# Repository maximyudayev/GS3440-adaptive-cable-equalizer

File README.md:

# SDI Adaptive Cable Equalizer - Semtech GS3440
This equalizer board was built as part of my Hardware Design course at KU Leuven - Campus GroupT in academic year 2020-2021, taught by the awesome Gorik :wink:

PCB front side:

PCB back side:

Mechanical layer details:

50 Ohm trace width:

75 Ohm trace width:

All the design files are under GPL3 and can be freely used for personal projects where this device can be of use.

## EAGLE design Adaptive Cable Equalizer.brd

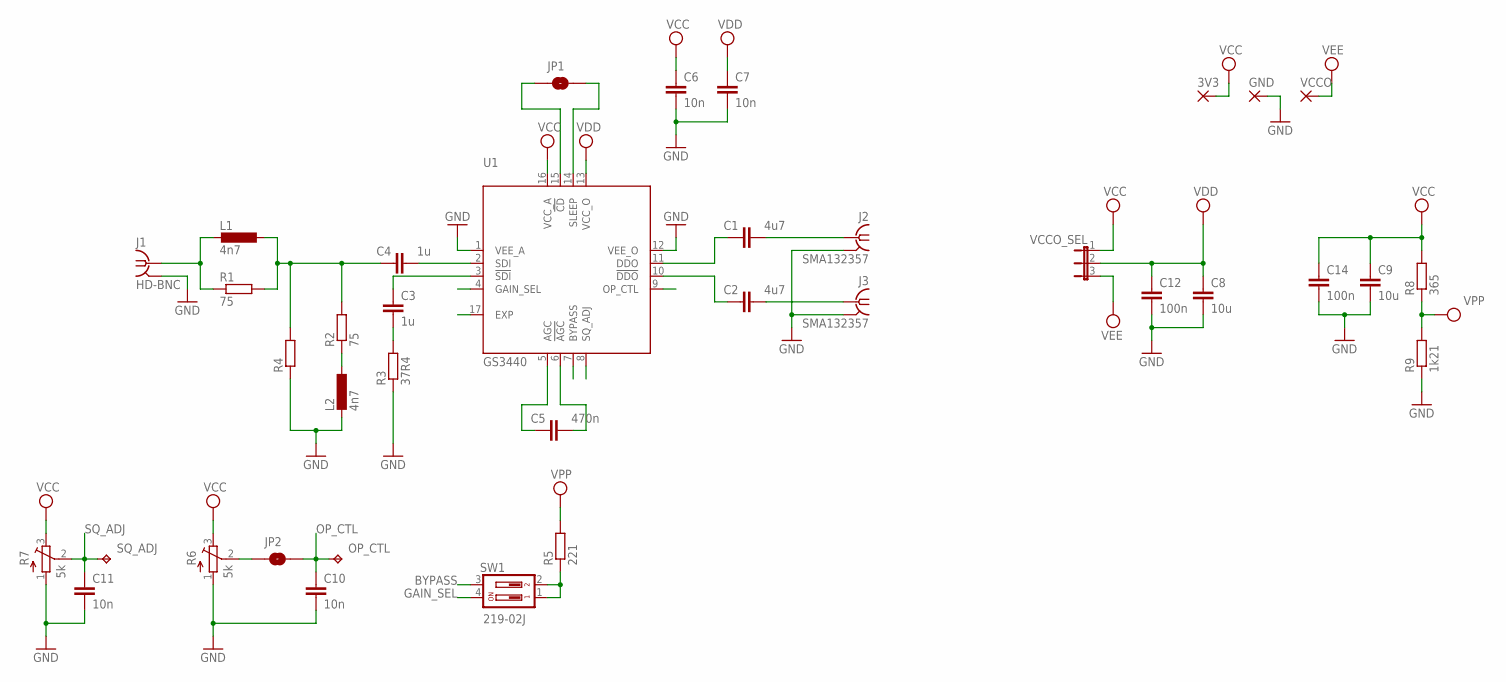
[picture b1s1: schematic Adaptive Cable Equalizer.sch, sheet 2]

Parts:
3V3: TAB_37800568(MSTIN); HOLE_1-3
C1, C2: 4u7; 0402
C3, C4: 1u; 0402
C5: 470n; 0402
C6, C7, C10, C11: 10n; 0402
C8, C9: 10u; C0805K
C12, C14: 100n; 0402
GND: TAB_37800568(MSTIN); HOLE_1-3
J1: HD-BNC; 034_1018_12G
J2, J3: SMA132357; SMA
JP1, JP2: SMD-JUMPER
L1, L2: 4n7; 0402
OP_CTL: TPTP06R; TP06R
R1, R2: 75; 0402
R3: 37R4; 0402
R4: R0402; 0402
R5: 221; 0402
R6, R7: 5k; 3223W
R8: 365; 0402
R9: 1k21; 0402
SQ_ADJ: TPTP06R; TP06R
SW1: 219-02J; CTS-219-02J
U1: GS3440; QFN65P400X400X90-17T260N
VCCO: TAB_37800568(MSTIN); HOLE_1-3
VCCO_SEL: JP2E; JP2

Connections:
!CD: JP1.P$1 (1), U1.15 (!CD)
BYPASS: SW1.3, U1.7 (BYPASS)
GAIN_SEL: SW1.4, U1.4 (GAIN_SEL)
GND: C6.2, C7.2, C8.2, C9.2, C10.2, C11.2, C12.2, C14.2, GND.P$1, J1.G@1 (2), J1.G@2 (2), J1.G@3 (2), J1.G@4 (2), J2.G@1 (2), J2.G@2 (2), J2.G@3 (2), J2.G@4 (2), J3.G@1 (2), J3.G@2 (2), J3.G@3 (2), J3.G@4 (2), L2.2, R3.1, R4.1, R6.1 (A), R7.1 (A), R9.1, U1.1 (VEE_A), U1.12 (VEE_O), U1.17 (EXP)
unnamed: C2.2, J3.1
unnamed: C1.2, J2.1
unnamed: C2.1, U1.10 (!DDO)
unnamed: C1.1, U1.11 (DDO)
unnamed: J1.P$1 (1), L1.2, R1.1
unnamed: C4.1, L1.1, R1.2, R2.2, R4.2
unnamed: C3.1, U1.3 (!SDI)
unnamed: C4.2, U1.2 (SDI)
unnamed: L2.1, R2.1
unnamed: C5.1, U1.5 (AGC)
unnamed: C3.2, R3.2
unnamed: C5.2, U1.6 (!AGC)
unnamed: JP2.P$1 (1), R6.2 (S)
unnamed: JP1.P$2 (2), U1.14 (SLEEP)
unnamed: R5.1, SW1.1, SW1.2
OP_CTL: C10.1, JP2.P$2 (2), OP_CTL.TP, U1.9 (OP_CTL)
SQ_ADJ: C11.1, R7.2 (S), SQ_ADJ.TP, U1.8 (SQ_ADJ)
VCC: 3V3.P$1, C6.1, C9.1, C14.1, R6.3 (E), R7.3 (E), R8.2, U1.16 (VCC_A), VCCO_SEL.1
VDD: C7.1, C8.1, C12.1, U1.13 (VCC_O), VCCO_SEL.2
VEE: VCCO.P$1, VCCO_SEL.3
VPP: R5.2, R8.1, R9.2

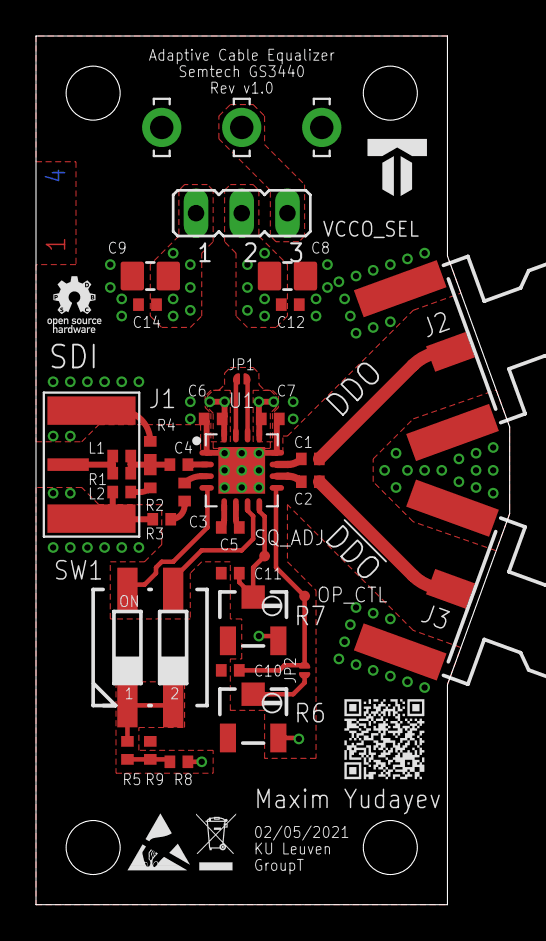
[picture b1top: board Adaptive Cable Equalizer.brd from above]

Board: 4 copper layers, 26.3 x 48.3 mm, 37 parts (0 on the bottom side), 25 nets.

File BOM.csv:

"Qty";"Value";"Device";"Package";"Parts";"Description";"";
"1";"";"JP2E";"JP2";"VCCO_SEL";"JUMPER";"";
"1";"";"R0402";"0402";"R4";"";"";
"2";"100n";"C0402";"0402";"C12, C14";"";"";
"4";"10n";"C0402";"0402";"C6, C7, C10, C11";"";"";
"2";"10u";"C-EUC0805K";"C0805K";"C8, C9";"CAPACITOR, European symbol";"";
"1";"1k21";"R0402";"0402";"R9";"";"";
"2";"1u";"C0402";"0402";"C3, C4";"";"";
"1";"219-02J";"219-02J";"CTS-219-02J";"SW1";"Surface Mount DIP Switch Series 219 SMT";"";
"1";"221";"R0402";"0402";"R5";"";"";
"1";"365";"R0402";"0402";"R8";"";"";
"1";"37R4";"R0402";"0402";"R3";"";"";
"1";"470n";"C0402";"0402";"C5";"";"";
"2";"4n7";"L0402";"0402";"L1, L2";"";"";
"2";"4u7";"C0402";"0402";"C1, C2";"";"";
"2";"5k";"TRIM_EU-3223W";"3223W";"R6, R7";"POTENTIOMETER";"";
"2";"75";"R0402";"0402";"R1, R2";"";"";
"1";"GS3440";"GS3440";"QFN65P400X400X90-17T260N";"U1";"Adaptive Cable Equalizer";"";
"1";"HD-BNC";"HD-BNC";"034_1018_12G";"J1";"HD BNC 75 Ohm";"";
"2";"SMA132357";"SMA132357";"SMA";"J2, J3";"SMA 50 Ohm End Launch Jack Receptacle - Round Contact";"";
"2";"SMD-JUMPER";"SMD-JUMPER";"SMD-JUMPER";"JP1, JP2";"";"";
"3";"TAB_37800568(MSTIN)";"TAB_37800568(MSTIN)";"HOLE_1-3";"3V3, GND, VCCO";"";"";
"2";"TPTP06R";"TPTP06R";"TP06R";"OP_CTL, SQ_ADJ";"Test pad";"";

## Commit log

2021-05-03 Full design upload. No stitching vias
    +: Schematic
    +: Board layout
    +: BOM
    +: Silkscreen artwork and QR-code
    +: Mechanical layer details, buildup and stackup
    +: Images
2021-05-03 Updated PCB images with better resolution
2021-05-03 Improved decoupling capacitor placement
    +: Added polygons for IC's VCC_A and VCC_O supplies
    +: Added multiple vias around distant "bulk" capacitors
